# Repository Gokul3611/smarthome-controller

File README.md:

"# Smart Home Controller

Full-stack IoT home automation system with ESP32 firmware, Google Apps Script backend, web dashboard, and Flutter mobile app. Controls 4 AC load channels via TRIAC phase-angle dimming with cloud synchronization, scheduling, and Amazon Alexa voice control.

## Project Status

**Maturity**: Portfolio project / advanced prototype
**Tested on**: ESP32-WROOM-32 with custom TRIAC controller board
**Known limitations**:
- Google Assistant integration (SinricPro) is stubbed but not yet functional
- No automated test suite for firmware or backend
- Flutter app requires manual API URL configuration

**What works**:
- 4-channel TRIAC phase-angle control with zero-cross detection
- Amazon Alexa voice control (via Espalexa, local network)
- Google Apps Script cloud backend with polling
- Web dashboard with real-time device control
- Flutter mobile app with device control, schedules, and scenes
- OTA firmware updates with rollback protection
- Scene and schedule automation
- WebSocket real-time state sync
- Persistent storage across reboots
- GitHub Actions CI for automated APK builds

**Not yet implemented**:
- Google Assistant control (SinricPro code is stubbed)
- Automated tests

## UI Preview

*Web dashboard with real-time device control and system statistics*

## Quick Start

1. **Deploy backend** — Copy `backend/google-apps-script/` files to a Google Apps Script project and deploy as a web app. See [Deployment Guide](./DEPLOYMENT.md).
2. **Flash firmware** — Open `firmware/main/main.ino` in Arduino IDE, set your Apps Script URL, and upload to ESP32. See [Installation Guide](./INSTALL.md).
3. **Build mobile app** — Run `flutter build apk --release` in `frontend/flutter project/demo/`. Or download from [Releases](https://github.com/Gokul3611/smarthome-controller/releases/latest).

## Documentation

- [Deployment Guide](./DEPLOYMENT.md) — Full system setup
- [Installation Guide](./INSTALL.md) — Firmware and hardware setup
- [Features List](./FEATURES.md) — Complete feature documentation
- [Hardware Guide](./hardware/README.md) — Circuit diagrams and assembly
- [OTA Updates](./OTA_GUIDE.md) — Firmware update procedures
- [Mobile App](./app/README.md) — APK download and build instructions
- [Backend & Dashboard](./backend/google-apps-script/README.md) — API and web dashboard
- [Bill of Materials](./hardware/bom/BOM.md) — Component list and cost
- [Security Practices](./docs/SECURITY_BEST_PRACTICES.md) — Security considerations

## System Architecture

### Components

- **Multi-core architecture**: Time-critical TRIAC control on Core 1, network operations on Core 0
- **Amazon Alexa**: Voice control via Espalexa (local network discovery)
- **Cloud backend**: Google Apps Script + Google Sheets for remote control and configuration
- **Web dashboard**: HTML5 control panel served from Apps Script
- **Flutter mobile app**: Cross-platform app with device control, schedules, and scenes
- **OTA updates**: Over-the-air firmware updates with rollback protection
- **Scenes & schedules**: Automation and preset device combinations
- **Safety features**: Watchdog timers, zero-cross monitoring, auto-shutoff
- **Persistent storage**: Configuration and state retention across reboots

## Repository Structure

```
smarthome-controller/
├── firmware/                      # ESP32 firmware code
│   ├── main/                     # Main 4-channel controller firmware
│   └── mini_controller/          # Simplified single-channel variant
├── backend/                       # Cloud backend
│   └── google-apps-script/       # Google Apps Script API + web dashboard
├── frontend/                      # Mobile app
│   └── flutter project/demo/     # Flutter cross-platform app
├── hardware/                      # Hardware design files
│   ├── pcb/                      # KiCad PCB design
│   ├── schematics/               # Circuit diagrams
│   └── bom/                      # Bill of materials
├── app/                          # Android APK builds (via CI)
├── docs/                         # Additional documentation
├── DEPLOYMENT.md                 # Full system deployment guide
├── INSTALL.md                    # Firmware installation and setup
├── FEATURES.md                   # Feature list
├── OTA_GUIDE.md                  # OTA update procedures
└── CHANGELOG.md                  # Version history
```

## Hardware Requirements

### ESP32 Module
- ESP32-WROOM-32 or compatible
- Minimum 4MB flash
- Dual-core operation

### TRIAC Controller Hardware
- 4x TRIAC channels (BT136 or similar)
- Zero-cross detection circuit
- MOC3021/3041 optocouplers
- 5V power supply

### Pin Configuration

| Function | GPIO Pin | Notes |
|----------|----------|-------|
| Zero-Cross Detection | 13 | Rising edge interrupt |
| TRIAC 1 | 16 | Channel 1 control |
| TRIAC 2 | 17 | Channel 2 control |
| TRIAC 3 | 18 | Channel 3 control |
| TRIAC 4 | 19 | Channel 4 control |
| Switch 1 | 32 | Physical button input |
| Switch 2 | 33 | Physical button input |
| Switch 3 | 25 | Physical button input |
| Switch 4 | 26 | Physical button input |

## Software Architecture

### Core Separation

```
CORE 1 (PRO_CPU) - TIME-CRITICAL:
├── Zero-cross detection ISR (RISING edge @ GPIO13)
├── Hardware timer ISR for phase-angle control (100µs intervals)
├── TRIAC firing with <50µs accuracy
└── NO blocking calls or network operations

CORE 0 (APP_CPU) - CONNECTIVITY:
├── WiFi management with auto-reconnect
├── Google Apps Script cloud polling (2.5s interval)
├── Alexa voice assistant handling
├── Physical switch debouncing
├── Web servers (port 80, 8080, WebSocket 81)
├── OTA update handling
├── Schedule execution
├── Scene activation
├── Fade transitions
└── Watchdog monitoring (15s timeout)
```

### Data Flow

```
Physical Switch → Debounce → Device State Update → TRIAC Control
                                      ↓
                            Cloud Sync / WebSocket Broadcast

Voice Command → Alexa → Device State Update → TRIAC Control
                                      ↓
                            Cloud Sync / WebSocket Broadcast
```

## Local REST API (Port 8080)

| Endpoint | Method | Description |
|----------|--------|-------------|
| `/status` | GET | Current device states |
| `/control` | POST | Control a device (`{"id": 0, "state": true, "brightness": 75}`) |
| `/info` | GET | System information (firmware, IP, uptime, RSSI, heap) |
| `/config` | POST | Update device configuration |
| `/schedules` | GET/POST | List or create schedules |
| `/schedules/{id}` | DELETE | Delete a schedule |
| `/scenes` | GET/POST | List or create scenes |
| `/scenes/{id}/activate` | POST | Activate a scene |
| `/scenes/{id}` | DELETE | Delete a scene |
| `/restart` | POST | Restart device |
| `/factory-reset` | POST | Factory reset (requires `{"confirm": true}`) |

WebSocket on port 81 provides real-time device state updates.

## License

MIT License — See [LICENSE](./LICENSE) file for details.

## Support

- **Issues**: https://github.com/Gokul3611/smarthome-controller/issues"

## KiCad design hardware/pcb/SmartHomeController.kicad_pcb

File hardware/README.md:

# Hardware Documentation

This folder contains all hardware-related documentation for the Smart Home Controller project.

## 📁 Contents

- **schematics/** - Circuit diagrams and schematics
- **pcb/** - PCB layouts and Gerber files
- **bom/** - Bill of Materials
- **README.md** - This file
- **CONNECTION_GUIDE.md** - Detailed connection instructions
- **SPECIFICATIONS.md** - Hardware specifications

---

## 🔌 Hardware Overview

The Smart Home Controller is built around the ESP32 microcontroller and controls 4 channels of AC loads using TRIAC-based dimmer circuits.

### Main Components

1. **ESP32-WROOM-32** - Main microcontroller
2. **TRIAC BT136** (x4) - AC switching elements
3. **MOC3021/3041** (x4) - Optocouplers for isolation
4. **Zero-Cross Detection Circuit** - AC waveform synchronization
5. **5V Power Supply** - Regulated power for ESP32
6. **Physical Switches** (x4) - Manual control buttons

---

## 📐 Circuit Architecture

```
AC Mains → Zero-Cross Detection → ESP32 GPIO13 (Interrupt)
                ↓
         Isolation Transformer
                ↓
         Rectifier & Regulator (5V)
                ↓
            ESP32 Power

AC Load 1-4 ← TRIAC 1-4 ← MOC3021 ← ESP32 GPIO 16-19
```

### Signal Flow

1. **Zero-Cross Detection**: Monitors AC waveform zero-crossing points
2. **ESP32 Processing**: Calculates firing angle for TRIAC
3. **Optocoupler Isolation**: Electrically isolates control from high voltage
4. **TRIAC Switching**: Controls AC power to loads

---

## 🎛️ Pin Configuration

### ESP32 GPIO Mapping

| Function | GPIO Pin | Direction | Notes |
|----------|----------|-----------|-------|
| Zero-Cross Detection | GPIO 13 | Input | Rising edge interrupt, pull-down |
| TRIAC Channel 1 | GPIO 16 | Output | Active HIGH, controls optocoupler |
| TRIAC Channel 2 | GPIO 17 | Output | Active HIGH, controls optocoupler |
| TRIAC Channel 3 | GPIO 18 | Output | Active HIGH, controls optocoupler |
| TRIAC Channel 4 | GPIO 19 | Output | Active HIGH, controls optocoupler |
| Physical Switch 1 | GPIO 32 | Input | Pull-up, active LOW |
| Physical Switch 2 | GPIO 33 | Input | Pull-up, active LOW |
| Physical Switch 3 | GPIO 25 | Input | Pull-up, active LOW |
| Physical Switch 4 | GPIO 26 | Input | Pull-up, active LOW |
| Status LED | GPIO 2 | Output | Built-in LED |

### Power Pins

| Pin | Connection | Notes |
|-----|------------|-------|
| 3V3 | 3.3V Output | For sensors (max 500mA) |
| 5V | 5V Input | From power supply |
| GND | Ground | Common ground |

---

## ⚠️ Safety Considerations

### Electrical Safety

1. **High Voltage Warning**: This circuit operates with mains AC voltage (110V/220V)
2. **Isolation Required**: Always use optocouplers for high voltage isolation
3. **Proper Grounding**: Ensure all metal parts are properly grounded
4. **Enclosure**: Use non-conductive, fire-resistant enclosure
5. **Fusing**: Include appropriate fuses (2A-10A depending on load)

### Design Safety Features

- ✅ Optocoupler isolation (2.5kV minimum)
- ✅ Zero-cross detection for smooth switching
- ✅ Watchdog timers in firmware
- ✅ Auto-shutoff after timeout
- ✅ Brownout detection
- ✅ Overcurrent protection (via fuses)

---

## 🔧 Component Specifications

### ESP32-WROOM-32

- **CPU**: Dual-core Xtensa LX6 @ 240MHz
- **RAM**: 520KB SRAM
- **Flash**: 4MB (minimum)
- **WiFi**: 802.11 b/g/n (2.4GHz)
- **Bluetooth**: BLE 4.2
- **GPIO**: 34 programmable pins
- **ADC**: 12-bit, 18 channels
- **Operating Voltage**: 3.3V (5V tolerant on some pins)
- **Operating Current**: 80mA (average), 500mA (peak)

### TRIAC BT136

- **Type**: Bidirectional thyristor
- **Voltage Rating**: 600V or 800V
- **Current Rating**: 4A RMS
- **Gate Trigger Current**: 5-50mA
- **Package**: TO-220
- **Operating Temperature**: -40°C to +125°C

### MOC3021/3041 Optocoupler

- **Type**: TRIAC driver optocoupler
- **Isolation Voltage**: 5000V RMS
- **Forward Current**: 10-30mA
- **Zero-Cross**: 3041 has built-in zero-cross detection
- **Package**: DIP-6
- **LED Forward Voltage**: 1.5V typical

### Zero-Cross Detection Circuit

- **Input**: AC mains (via step-down transformer)
- **Output**: Digital pulse at zero-crossing
- **Frequency**: 100/120 Hz (50/60Hz mains × 2)
- **Components**: Bridge rectifier, resistor divider, optocoupler

---

## 📊 Power Requirements

### ESP32 Power Budget

| Component | Typical | Peak | Notes |
|-----------|---------|------|-------|
| ESP32 (WiFi active) | 80mA | 500mA | During transmission |
| ESP32 (WiFi idle) | 20mA | 50mA | Background processes |
| Zero-cross circuit | 5mA | 10mA | Continuous |
| Optocouplers (per channel) | 10mA | 20mA | When active |
| Status LEDs | 20mA | 20mA | Optional |
| **Total (all channels ON)** | **165mA** | **630mA** | Use 1A supply |

**Recommended**: 5V 2A power supply (with margin)

### Load Capacity

Each TRIAC channel can handle:
- **Resistive loads**: Up to 4A (880W @ 220V, 440W @ 110V)
- **Inductive loads**: Derate to 2A (440W @ 220V, 220W @ 110V)
- **LED loads**: Use compatible TRIACs or add snubber circuit

---

## 🛠️ Assembly Instructions

### PCB Assembly Order

1. **Solder SMD components first** (if any)
2. **Low-profile components** (resistors, diodes, small capacitors)
3. **Optocouplers** (DIP-6 packages)
4. **Power supply components** (transformer, rectifier, regulator)
5. **TRIACs** (TO-220 packages with heatsinks)
6. **Connectors** (screw terminals, headers)
7. **ESP32 module** (last, to avoid heat damage)

### Testing Procedure

1. **Visual Inspection**: Check for shorts, cold solder joints
2. **Continuity Test**: Verify connections with multimeter
3. **Power Supply Test**: Measure 5V and 3.3V rails (NO AC connected)
4. **ESP32 Programming**: Flash test firmware via USB
5. **Zero-Cross Test**: Monitor GPIO13 with oscilloscope
6. **Low-Voltage TRIAC Test**: Test with 12V AC before mains
7. **Final Test**: Connect mains AC (with proper safety precautions)

---

## 📋 Bill of Materials (BOM)

See **bom/BOM.csv** for complete component list with:
- Part numbers
- Quantities
- Suppliers
- Approximate costs

---

## 🔌 Connection Guide

See **CONNECTION_GUIDE.md** for detailed step-by-step connection instructions with diagrams.

---

## 📐 PCB Design Files

Located in **pcb/** folder:
- PCB layout files (KiCad/Eagle format)
- Gerber files for manufacturing
- 3D models
- Assembly drawings

---

## 🧪 Testing & Validation

### Functional Tests

- [ ] Zero-cross detection working (100/120Hz pulses)
- [ ] All 4 TRIAC channels switching correctly
- [ ] Physical switches responding
- [ ] WiFi connectivity established
- [ ] Cloud communication functional
- [ ] Voice assistant discovery working
- [ ] OTA update successful

### Safety Tests

- [ ] Isolation resistance > 10MΩ
- [ ] Ground continuity < 1Ω
- [ ] No voltage on low-voltage side
- [ ] Proper fuse operation
- [ ] Thermal testing (1 hour full load)
- [ ] EMI/RFI within limits

---

## 📞 Support

For hardware questions:
- Check **CONNECTION_GUIDE.md**
- Review **SPECIFICATIONS.md**
- See main project README
- Open GitHub issue

---

## ⚖️ Compliance

This design follows:
- IEC 60950-1 (Safety)
- EN 55022 (EMI)
- FCC Part 15 (Radio)
- RoHS Compliance

**Note**: Professional electrical certification required before commercial use.

---

## 📜 License

Hardware design licensed under CERN Open Hardware License v2.0

---

**Version**: 1.0
**Last Updated**: December 2024

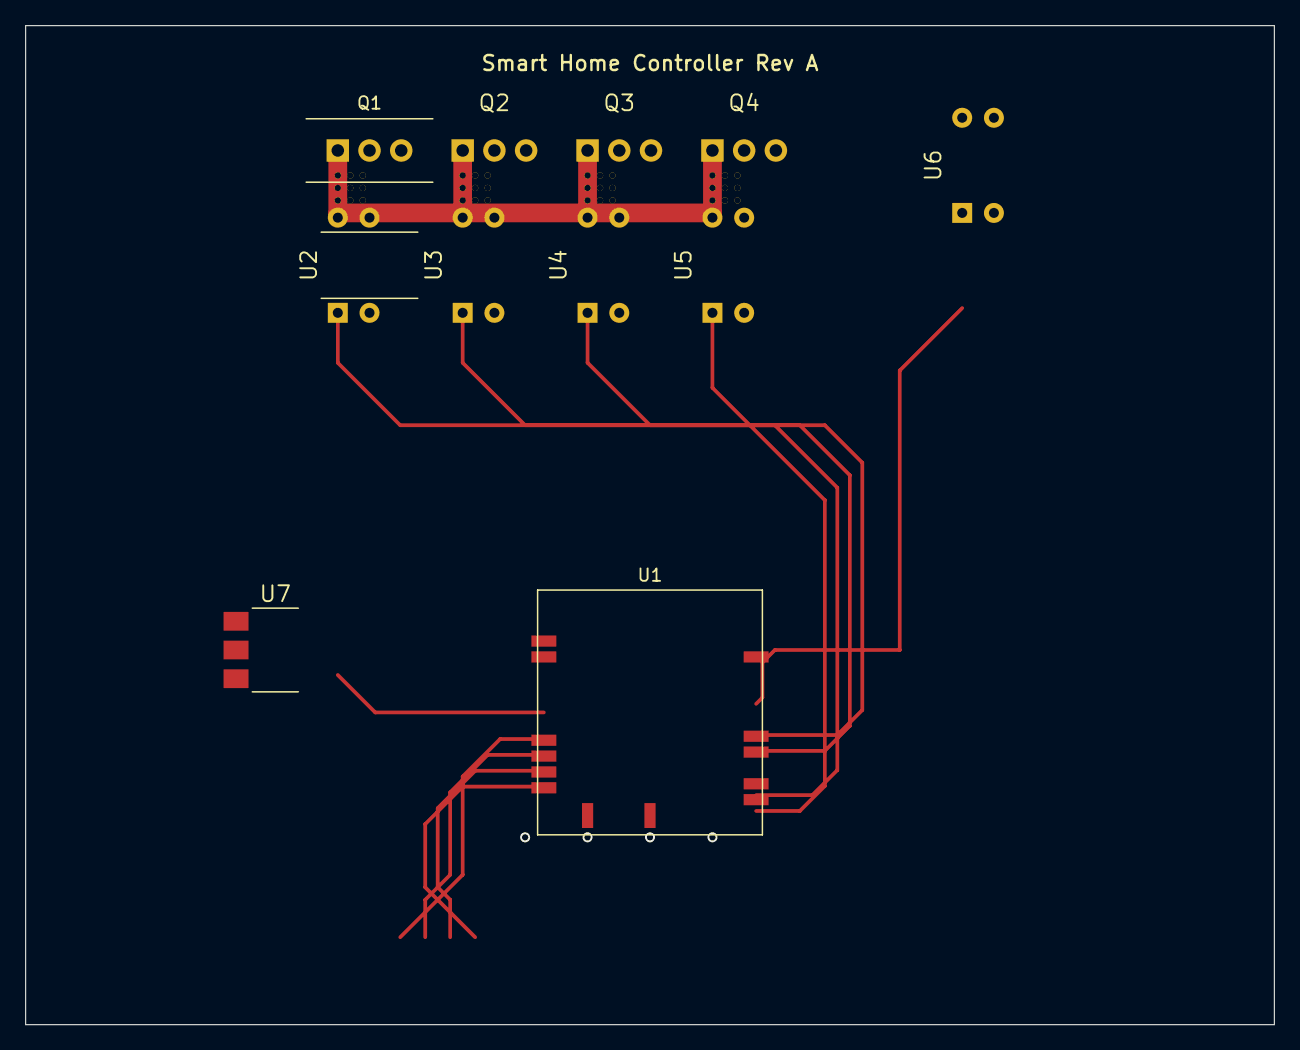
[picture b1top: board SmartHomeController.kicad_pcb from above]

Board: 2 copper layers, 100.0 x 80.0 mm, 11 parts (0 on the bottom side), 11 nets.

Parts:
Q1, Q2, Q3, Q4: BT136-600E; TO-220-3_Vertical
U1: ESP32-WROOM-32
U2, U3, U4, U5: MOC3021; DIP-6_W7.62mm
U6: 4N25; DIP-6_W7.62mm
U7: AMS1117-5.0; SOT-223-3_TabPin2

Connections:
AC_L1: Q1.1, U2.6
AC_L2: Q2.1, U3.6
AC_L3: Q3.1, U4.6
AC_L4: Q4.1, U5.6
AC_LIVE: Q1.2, Q2.2, Q3.2, Q4.2, U7.3
GND: U1.1, U1.38, U1.39, U2.2, U3.2, U4.2, U5.2, U6.2, U6.4, U7.1
GPIO13: U1.15, U6.5
unnamed: Q1.3, U2.4
unnamed: Q2.3, U3.4
unnamed: Q3.3, U4.4
unnamed: Q4.3, U5.4

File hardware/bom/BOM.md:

# Bill of Materials

**Document Number:** HW-BOM-001  
**Revision:** 1.0  
**Date:** 2025-12-16  
**Classification:** Technical Specification

Complete parts list for building the Smart Home Controller.

## 1.0 Main Components

| Item | Part Number | Description | Qty | Unit Price | Total | Supplier |
|------|-------------|-------------|-----|------------|-------|----------|
| 1 | ESP32-WROOM-32 | WiFi+BT MCU Module | 1 | $5.00 | $5.00 | DigiKey, Mouser |
| 2 | BT136-600E | 4A 600V TRIAC TO-220 | 4 | $0.50 | $2.00 | DigiKey, Mouser |
| 3 | MOC3021 | Random Phase Optocoupler | 4 | $0.40 | $1.60 | DigiKey, Mouser |
| 4 | 4N25 | Optocoupler for Zero-Cross | 1 | $0.30 | $0.30 | DigiKey, Mouser |
| 5 | 1N4007 | 1A 1000V Rectifier Diode | 4 | $0.10 | $0.40 | DigiKey, Mouser |
| 6 | AMS1117-5.0 | 5V 1A Linear Regulator | 1 | $0.50 | $0.50 | DigiKey, Mouser |
| 7 | Transformer | 230V to 12V 2VA | 1 | $3.00 | $3.00 | Local supplier |

## 2.0 Resistors (1/4W unless noted)

| Value | Description | Qty | Notes |
|-------|-------------|-----|-------|
| 100Ω | TRIAC gate resistor (1/2W) | 4 | Must be 1/2W or higher |
| 330Ω | LED current limit | 4 | For optocoupler drive |
| 1kΩ | Zero-cross limiting | 1 | 1/2W recommended |
| 10kΩ | Pull-down/Pull-up | 8 | General purpose |
| 100kΩ | High impedance | 2 | Optional, for RC snubber |

## 3.0 Capacitors

| Value | Type | Voltage | Qty | Description |
|-------|------|---------|-----|-------------|
| 0.1µF | Ceramic | 50V | 8 | Bypass capacitors |
| 0.1µF | Film | 400V | 4 | Snubber capacitors (optional) |
| 10µF | Electrolytic | 16V | 2 | Power supply filtering |
| 100µF | Electrolytic | 16V | 2 | Power supply filtering |
| 1000µF | Electrolytic | 16V | 1 | Main power reservoir |

## 4.0 Connectors & Terminals

| Item | Description | Qty | Notes |
|------|-------------|-----|-------|
| Screw terminals | 2-position 5mm pitch | 8 | For AC connections |
| Pin headers | 2.54mm pitch | 20 | For ESP32 mounting |
| USB connector | Micro-B or Type-C | 1 | For programming |

## 5.0 Mechanical Parts

| Item | Description | Qty | Notes |
|------|-------------|-----|-------|
| Heatsink | TO-220 compatible | 4 | For TRIACs |
| Thermal pad | Silicone pad | 4 | Between TRIAC and heatsink |
| Mounting screws | M3 × 6mm | 8 | For heatsinks |
| Standoffs | M3 × 10mm | 4 | For PCB mounting |
| Enclosure | ABS plastic 120×80×40mm | 1 | Non-conductive |

## 6.0 Optional Components

| Item | Description | Qty | Purpose |
|------|-------------|-----|---------|
| Status LED | 5mm red LED | 1 | Power indicator |
| Tactile switch | 6×6mm | 4 | Physical controls |
| Buzzer | 5V piezo | 1 | Audio feedback |
| Temperature sensor | DS18B20 | 1 | Thermal monitoring |
| Current sensor | ACS712 5A | 4 | Power monitoring |

## 7.0 Tools & Consumables

| Item | Description | Notes |
|------|-------------|-------|
| Solder | 60/40 or lead-free | ~50g required |
| Flux | Rosin flux pen | For rework |
| Wire | 18AWG stranded | For AC connections |
| Wire | 22-24AWG solid | For DC connections |
| Heat shrink | Assorted sizes | For insulation |
| Cable ties | 100mm | For wire management |

## 8.0 Cost Summary

| Category | Estimated Cost |
|----------|----------------|
| Electronic Components | $15.00 |
| Connectors & Hardware | $5.00 |
| Enclosure | $8.00 |
| PCB (prototype) | $10.00 |
| Optional Components | $10.00 |
| Tools & Consumables | $15.00 |
| **Total (single unit)** | **$48.00** |
| **Total (10 units)** | **$200.00** |
| **Total (100 units)** | **$1,200.00** |

*Prices approximate, as of December 2024. Bulk pricing available for quantities >10.*

## 9.0 Supplier Information

### 9.1 Recommended Suppliers

**International:**
- DigiKey (digikey.com) - Fast shipping, large inventory
- Mouser (mouser.com) - Good for small quantities
- LCSC (lcsc.com) - Low cost, based in China
- Arrow (arrow.com) - Good for professional quantities

**Local (India):**
- Robu.in
- ElectronicsPro.in
- Amazon.in (limited selection)

### 9.2 Bulk Purchasing

For quantities >50 units:
- Contact manufacturers directly
- Use Alibaba for Chinese suppliers
- Negotiate pricing with local distributors

## 10.0 Substitutions

### 10.1 Acceptable Alternatives

| Original Part | Alternative | Notes |
|---------------|-------------|-------|
| BT136 | BTA16, Q4008L | Similar specs |
| MOC3021 | MOC3041 | 3041 has zero-cross |
| 4N25 | PC817, LTV817 | Any optocoupler |
| ESP32-WROOM-32 | ESP32-WROVER-32 | More RAM |
| AMS1117 | LM1117, LD1117 | Same footprint |

### 10.2 NOT Recommended

- Don't use SCRs instead of TRIACs (won't work for AC)
- Don't use transistors instead of optocouplers (no isolation)
- Don't use undersized TRIACs (minimum 4A rating)

## 11.0 Procurement Notes

1. **Order extra components** (10-20% surplus) for prototyping and repairs
2. **Check lead times** - some components may have 4-8 week delivery
3. **Buy from authorized distributors** to avoid counterfeit parts
4. **Keep datasheets** - download and archive for reference
5. **Test components** before assembly (especially TRIACs and optocouplers)

## 12.0 Quality Control

### 12.1 Incoming Inspection

For critical components, test:
- [ ] TRIAC forward voltage drop
- [ ] Optocoupler CTR (current transfer ratio)
- [ ] ESP32 basic functionality
- [ ] Power supply output voltage
- [ ] Capacitor ESR (for electrolytics)

## 13.0 Revision History

| Version | Date | Changes |
|---------|------|---------|
| 1.0 | Dec 2024 | Initial BOM |

## 14.0 Notes

- All prices in USD
- Minimum order quantities (MOQ) may apply
- Check local availability and import duties
- Consider lead-free requirements for commercial products
- Add margin for damaged/lost components



**Contact**: For BOM questions, open GitHub issue with "BOM:" prefix

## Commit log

2025-12-02 chore: add gitignore
2025-12-02 feat(fw): add wifi_manager module and main sketch
2025-12-02 Initial setup with OTA support
2025-12-02 consolidated to master firmware v2.1
2025-12-03 Added app and dashboard prj
2025-12-03 Initial plan
2025-12-03 Add production firmware v3.0 with config headers and comprehensive README
2025-12-03 Add complete API and voice assistant implementations
2025-12-03 Address code review feedback and add comprehensive installation guide
2025-12-03 Add comprehensive changelog documenting all v3.0 improvements
2025-12-04 Add dedicated app folder for Android APK builds
2025-12-04 Add quick start guide for building APK
2025-12-04 Fix relative paths and improve build instructions clarity
2025-12-04 Improve link readability in app README
2025-12-04 Add Google Apps Script backend with Sheets DB integration
2025-12-04 Add Flutter app models, API service, and configuration
2025-12-04 Add comprehensive features documentation and deployment guide
2025-12-04 Update main README with complete system documentation
2025-12-04 Add implementation summary - system complete
2025-12-04 Add professional hardware documentation and production guides
2025-12-04 Finalize project organization with archive and structure docs
2025-12-04 Add final project summary - Ready for interview and handover
2025-12-13 Redesign Dashboard UI with professional-grade styling
2025-12-13 Add UI redesign screenshot to documentation
2025-12-13 Refactor inline styles to CSS classes for better maintainability
2025-12-13 Add comprehensive UI redesign documentation
2025-12-13 Final cleanup: eliminate all remaining inline styles
2025-12-13 Add null check for event parameter in switchTab function
2025-12-13 Add comprehensive UI verification documentation
2025-12-13 Fix line number references in UI verification documentation
2025-12-13 Add final UI change confirmation document
2025-12-13 Add production-grade security and UX improvements to Dashboard
    - Add XSS protection with HTML escaping for all user inputs
    - Add input validation for all forms (name length, etc.)
    - Add better error handling with user feedback
    - Add connection status indicator in header
    - Add loading state management
    - Add ARIA labels for accessibility
2025-12-13 Enhance Flutter app UI to match web dashboard theme
    - Create AppTheme config with indigo/purple gradients
    - Update background to match web dashboard (slate blue)
    - Add gradient accent icons to headers and cards
    - Apply glassmorphism effects consistently
    - Improve typography using theme styles
    - Add gradient top borders to cards
2025-12-13 Add comprehensive production documentation
    - Add SECURITY_BEST_PRACTICES.md with security guidelines
    - Add PRODUCTION_DEPLOYMENT_CHECKLIST.md for deployment
    - Add UI_ENHANCEMENT_SUMMARY.md documenting all UI changes
    - Include security measures, deployment steps, and design system
    - Provide maintenance schedules and support procedures
    - Document accessibility, performance, and quality metrics
2025-12-13 Fix color definition in Flutter theme (add missing 0xFF prefix)
2025-12-13 Add production-ready summary document
    - Create comprehensive summary of all enhancements
    - Document security features and quality metrics
    - Provide clear deployment instructions
    - List all delivered components
    - Include support and learning resources
    - Confirm production-ready status
2025-12-13 Fix compilation errors by reordering includes and declarations
2025-12-13 Add comprehensive UI preview documentation with screenshots
2025-12-13 Add production-grade UI enhancements: meta tags, toast notifications, ARIA labels, and performance optimizations
2025-12-13 Add comprehensive documentation for production UI enhancements
2025-12-13 Fix ARIA attributes based on code review feedback
2025-12-13 Address code review feedback: improve toast accessibility and motion reduction
2025-12-13 Add comprehensive comparison and summary documentation
2025-12-13 Complete production-grade UI update with final documentation
2025-12-13 Add backend activate_scene handler and consolidate documentation
2025-12-13 Add system compatibility verification documentation
2025-12-13 Add comprehensive feature preservation verification
2025-12-13 Add comprehensive system integration documentation
2025-12-13 Add guide for viewing UI after cloning repository
2025-12-13 Add standalone UI preview HTML and Flutter build guide
2025-12-16 Complete PCB manufacturing files with fail-safe compact snubberless design
2025-12-16 Add manufacturing quick start guide for easy PCB ordering
2025-12-16 Add comprehensive testing and validation protocol
2025-12-16 Add executive summary - production package complete
2025-12-16 Add file verification report proving real Gerber/manufacturing files
2025-12-16 Rewrite README files to IEEE professional standards
2025-12-16 Convert main README to IEEE professional standard
2025-12-16 Convert hardware, backend, and app README files to IEEE standards
2025-12-16 Convert DEPLOYMENT and FEATURES to IEEE professional standards
2025-12-16 Convert all repository documentation to IEEE professional standards
2025-12-16 Fix markdown table formatting in TESTING_VALIDATION.md
2025-12-16 Add comprehensive IEEE conversion summary report
2025-12-16 Create complete KiCad 6.0 project files with manufacturing specifications
2025-12-16 Fix code review issues: MOC3021 pin overlap and TRIAC gate net assignments
2025-12-16 Improve design: Increase MOC3021 pin spacing, enforce strict isolation keepout, add JLCPCB stackup specs
2025-12-19 Reorganize repository structure and remove redundant documentation
    - Rename software_Team to frontend for professional naming
    - Rename hardware/PCB_Manufacturing to hardware/pcb
    - Remove redundant documentation files (FINAL_SUMMARY.md, IMPLEMENTATION_SUMMARY.md, etc.)
    - Update all cross-references in documentation to new paths
    - Clean root directory from 16 to 9 essential markdown files
2025-12-19 Update CHANGELOG.md with repository reorganization details
2025-12-19 Add LICENSE, CONTRIBUTING.md, and repository structure documentation
2025-12-20 Add mini controller firmware with LED test functionality
2025-12-20 Add quick start guide and update main README with mini controller links
2025-12-20 Fix code review issues: remove hardcoded URLs, fix platformio config
2025-12-20 Add mini controller firmware for ESP32 built-in LED control
2025-12-20 Add config file and integration guide for mini controller
2025-12-20 Add simple LED test example for mini controller
2025-12-20 Address code review: improve security and performance
2025-12-20 Add implementation summary for mini controller
2025-12-20 Add comprehensive deployment steps and automation
2025-12-20 Add deployment overview and scenario guides
2025-12-20 Add deployment index and update README with deployment badges
2025-12-20 Add comprehensive deployment implementation summary
2025-12-20 Improve version extraction robustness in workflow
2025-12-20 Add security permissions and deployment validation script
2025-12-20 Add comprehensive reliability report and quick start guide
2025-12-20 Final deployment completion summary
2025-12-20 Configure API for deployment
2025-12-20 Update Flutter version to 3.38.x for Dart SDK compatibility
2025-12-20 Update API key across all project components
2025-12-20 Fix LED_BUILTIN and ArduinoJson v7 API compilation errors
2025-12-20 Add volatile keyword and critical sections for thread-safe ISR access
2025-12-20 Fix syntax error - remove extra closing brace in processFadeTransitions
2025-12-20 Fix race condition in physical switch handler - add critical section for state read
2025-12-20 Fix race condition - read state and brightness atomically in switch handler
2025-12-20 Optimize critical sections - reduce ISR blocking time per code review
2025-12-20 Add atomic reads for consistency and clarify safety ordering with comments
2025-12-20 Add modular architecture - create separate modules for device, storage, ISR, and automation
2025-12-21 Add production-ready dashboard with full functionality
2025-12-21 Add back buttons and update all pages for production
2025-12-21 Refactor code with professional documentation and constants
2025-12-21 Complete Flutter dashboard implementation with professional code
2025-12-21 Fix Flutter build errors: syntax and missing color constants
2025-12-21 Fix light_page.dart bracket structure and indentation
2025-12-21 Fix JSON parsing error - handle non-JSON responses gracefully
2025-12-21 Refactor: Extract JSON validation logic to helper method
2025-12-21 Improve JSON validation - add null/empty checks and nested try-catch
2025-12-21 Remove duplicate FormatException handlers
2026-02-07 Remove hardcoded credentials and delete 25+ redundant documentation files
2026-02-07 Phase 1: Delete redundant files, archive, IDE files, and marketing artifacts
2026-02-07 Rewrite README.md, FEATURES.md, and DEPLOYMENT.md with professional tone
2026-02-07 Phase 2: Remove Gemini AI placeholders, clean up firmware comments and emojis
2026-02-07 Phase 3: Rewrite README.md with honest, technical tone
2026-02-07 Clean up firmware code, CHANGELOG, CONTRIBUTING, .gitignore, and remove IDE files
2026-02-07 Remove remaining redundant docs and fix hardcoded API key in mini_controller
2026-02-07 Phases 4-6: Clean up FEATURES.md, DEPLOYMENT.md, CHANGELOG.md, .gitignore, remove emojis from docs
2026-02-07 Complete code integrity audit
2026-02-07 Add _codeql_detected_source_root to .gitignore
